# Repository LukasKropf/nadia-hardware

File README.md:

# NADIA - Hardware

- 3 galvanisch getrennte RS-232 Schnittstellen, [MAX33250EELC+](https://media.digikey.com/pdf/Data%20Sheets/Maxim%20PDFs/MAX33250E_51E_Rev1_Nov2018.pdf)
- 5 digitale Eingänge
- 5 analoge Eingänge
- 3 galvanisch getrennte Ausgänge (Solid State Relais, [G3VM-61GR2](https://omronfs.omron.com/en_US/ecb/products/pdf/en-g3vm_41gr8_61gr.pdf))
- Galvanisch getrennte PoE Speisung

## Übersicht

``` mermaid
flowchart LR
    A[M12 Ethernet mit PoE] --- B[NADIA]
    B --- C[5 Digitale Eingänge]
    B --- D[5 Analoge Eingänge]
    B --- E[3 RS-232 Schnittstellen]
    B --- F[3 Digitale Ausgänge]    
    G[Optionale Speisung] -.- B
    H[micro-USB] -.- B
    I[micro-SD Karte] --- B
    
```
|NADIA im Gehäuse | NADIA PCB |
|-|-|
|  ||

## Rechnerplatine

| Wert                                      | Wert       | Einheit |
|:------------------------------------------|------------|---------|
| Rechnerplatine  [Pocketbeagle](https://beagleboard.org/pocket)                          |  |   -    |
| RAM                                       |  512       | MB,  DDR3 RAM|
| CPU  [Octavo Systems OSD3358-SM](http://octavosystems.com/octavo_products/osd335x-sm/)          |  1         | GHz           |
| Speicher                                  |  -         | microSD       |

## Elektrische Charakteristik

| Wert                                      | Min  | Typisch  | Max       | Einheit |
|:------------------------------------------|------|:--------:|-----------|---------|
| Speisung Spannung                         | 36   | 48       | 56        | VDC       |
| Speisung Strom                            |      | 50       | 100       | mA      |
| Galvanische Trennung Speisung             |      |          | 1.5       | kV      |
| **Digitaler Eingang**                     |
| Schmitt-Trigger [74HC7014D](https://www.mouser.ch/datasheet/2/916/74HC7014-1598223.pdf)    |
| Digitaler Eingang Pegel High              |      | 4        |           | VDC       |
| Digitaler Eingang Pegel Low               |      | 3.8      |           | VDC       |
| Digitaler Eingang maximale Spannung       | -100 |          | 100       | VDC       |
| Digitaler Eingang Eingangswiderstand      | 560  |          | 660       | kΩ      |
| **Analoger Eingang**                      |
| Spannungsteiler mit Widerständen|
| Analoger Eingang maximale Spannung        | -100 |          | 100       | VDC       |
| Analoger Eingang Messbereich / V          | 0    |          | 50        | VDC       |
| Analoger Eingang Eingangswiderstand       | 560  |          | 850       | kΩ      |
| Analoger Eingang Bandbreite -3dB          |      | 300      |           | Hz      |
| **Digitaler Ausgang**                     |
| Solid State Relais [G3VM-61GR2](https://omronfs.omron.com/en_US/ecb/products/pdf/en-g3vm_41gr8_61gr.pdf) |
| Digitaler Ausgang Spannung                |      |          | 60        | Vpeak AC/DC   |
| Digitaler Ausgang Strom                   |      |          | 1.7       | A       |
| Digitaler Ausgang Schaltfrequent          |      |          | 10        | Hz      |
| Digitaler Ausgang Isolationsspannung      |      |          | 1.5       | kV_rms  |
| **RS-232 Schnittstelle**                  |
| Treiber  [MAX33250EELC+](https://media.digikey.com/pdf/Data%20Sheets/Maxim%20PDFs/MAX33250E_51E_Rev1_Nov2018.pdf)| ||||
| RS-232 Schnittstelle Galvanische Trennung |      | 200      | 600 @ 60s | Vrms    |
| RS-232 ESD Schutz                         |      |          | ±15       | kV      |
| RS-232 Eingangswiderstand                  | 3    | 5        | 7         | kΩ      |
| RS-232 Eingangsspannung                    |      |          | ±25       | V       |
| RS-232 Ausgangsspannung                   |      | ±5 @ 3kΩ | ±13.2     | V       |
| RS-232 Ausgangskurzschlussstrom          |      |          | ±70       | mA      |

## Konnektivität

### Ethernet

Die Ethernetverbindung wird NADIA intern über einen USB-Ethernet Wandler sichergestellt, dem [LAN9500A von Microchip](https://www.microchip.com/en-us/product/LAN9500A).

Über Ethernet kann auf alle Dienste von NADIA zugegriffen werden.

### Micro USB

Auf NADA kann über die Micro USB Schnittstelle zugegriffen werden. NADIA erstellt über USB eine virtuelle Ethernet-Verbindung her.
Mehr Details siehe die Dokumentation von Beagleboard Pocketbeagle:

- [Getting Started - Enable a network connection](https://beagleboard.org/getting-started#step2)
- [Pocketbeagle System Reference Manual](https://github.com/beagleboard/pocketbeagle/wiki/System-Reference-Manual#533-usb-20-connector)

Über USB kann auf alle Dienste von NADIA zugegriffen werden.

### Wireless

NADIA verfügt über keine Wireless Kommunikationsmöglichkeiten.

### CAN

NADIA verfügt in dieser Version über **kein** CAN.
Allerdings verfügt das Pocketbeagle über die Möglichkeit zwei CAN Schnittstellen anzubinden. Dies würde ein neues PCB-Layout voraussetzen.

### Serial RS232

Die drei seriellen Schnittstellen sind jeweils galvanisch getrennt von der Speisung. Aus Sicherheitsgründen müssen die Schnittstellen über einen GPIO Pin freigeschaltet werden, bevor sie benutzt werden können.

## Software

Als Basisimage dient das Image von Pocketbeagle:
[AM3358 Debian 10.3 2020-04-06 4GB SD IoT](https://beagleboard.org/latest-images)
Um einen zuverlässigen Betrieb sicherzustellen, ist die Erstellung von verschiedenen Partitionen nötig. Die Systempartition in ReadOnly.

[Node-RED](https://nodered.org/) wird für das eigentliche Programmieren verwendet.
Mit Node-RED können auch sehr einfach ansprechende GUIs erstellt werden.

Auf NADIA, respektive dem PocketBeagle, ist auch jede andere ARMHF Linux Software lauffähig.

Beispiele: (jedoch noch keine Erfahrung)

- [OpenPLC](https://www.openplcproject.com/)
- [4DIAC](https://www.eclipse.org/4diac/)

# Licence

Copyright Lukas Kropf 2022.

This source describes Open Hardware and is licensed under the CERN-OHL-W v2  or later.

You may redistribute and modify this documentation and make products
using it under the terms of the CERN-OHL-W v2 (https:/cern.ch/cern-ohl).

This documentation is distributed WITHOUT ANY EXPRESS OR IMPLIED
WARRANTY, INCLUDING OF MERCHANTABILITY, SATISFACTORY QUALITY
AND FITNESS FOR A PARTICULAR PURPOSE. 
Please see the CERN-OHL-W v2 for applicable conditions.

Source location: https://github.com/LukasKropf/nadia-hardware

As per CERN-OHL-W v2 section 4.1, should You produce hardware based on
these sources, You must maintain the Source Location visible on the
external case of NADIA-Hardware or other product you make using
this documentation.

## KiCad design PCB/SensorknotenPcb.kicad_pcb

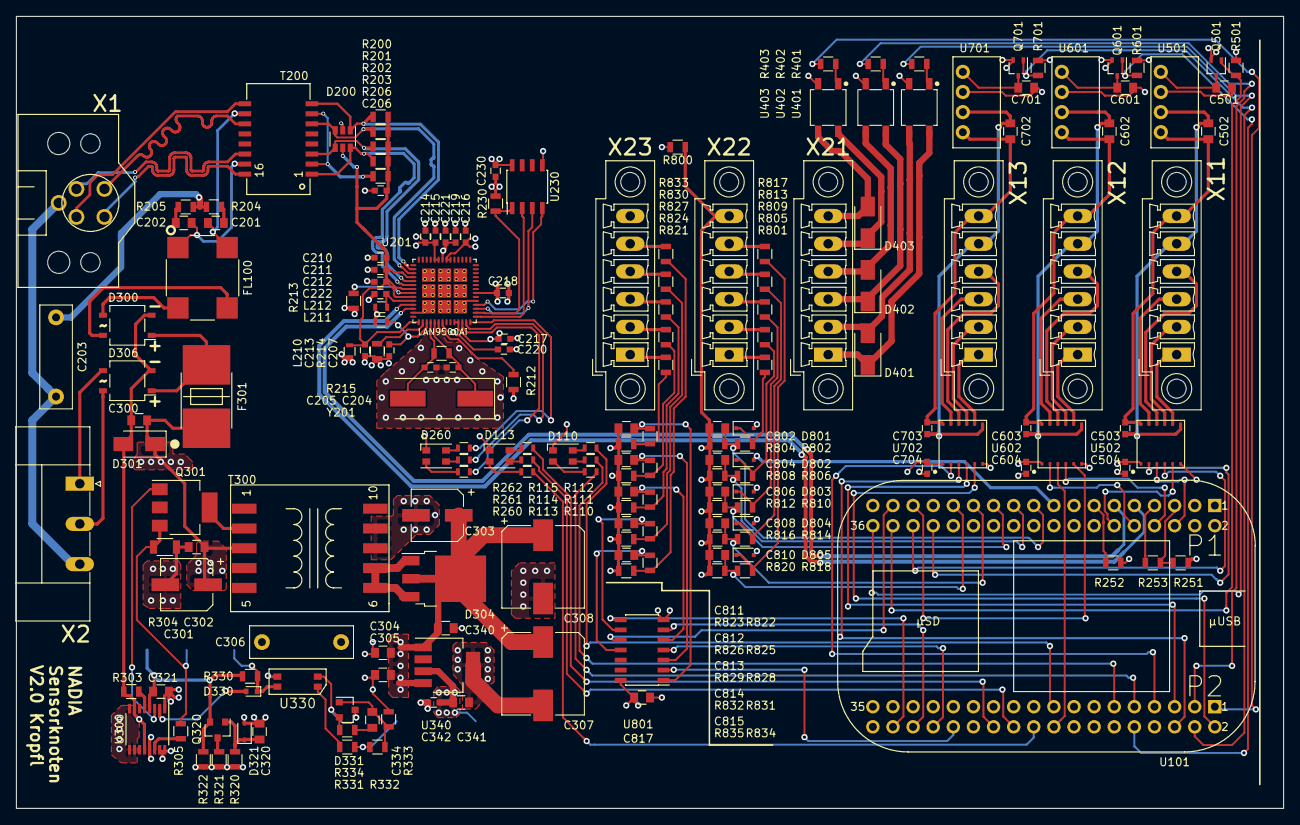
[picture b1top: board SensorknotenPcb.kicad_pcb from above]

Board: 4 copper layers, 160.0 x 100.0 mm, 193 parts (0 on the bottom side), 161 nets.

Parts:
C201, C202: 22n/200V; C_0805
C203, C306: 1n/2kV; C_Rect_L13.0mm_W4.0mm_P10.00mm_FKS3_FKP3_MKS4
C204, C205: 33pF 50V; C_0603
C206, C207, C210, C211, C212, C213, C214, C215, C216, C217, C218, C219, C220, C221, C222, C230, C342, C503, C504, C603, C604, C703, C704: 0.1µF; C_0603
C300: 0.1µF 100V; C_0805
C301: 10µF 63V; CP_Elec_6.3x5.8
C302: 1µF; C_0805
C303: 330µF; CP_Elec_6.3x5.8
C304, C305, C321, C340, C341, C501, C502, C601, C602, C701, C702, C817: 10µF; C_0805
C307, C308: 1500µF; CP_Elec_10x10
C320, C802, C804, C806, C808, C810, C811, C812, C813, C814, C815: 47nF; C_0805
C334: 6.8nF; C_0805
D110, D113, D260: LED_ARGB; LED_Cree-PLCC4_3.2x2.8mm_CCW
D200: WE-TVS_5V; SOT-23-6
D300, D306: D_Bridge_+-AA; Diode_Bridge_TO-269AA
D301: TVS 58V; D_SMA
D304: D_Schottky; TO-252-3_TabPin2
D321: 9.1V; D_SOD-323
D330: Fast Recovery; D_SOD-523
D331: TLV431BCDBZR; SOT-23
D401, D402, D403: TVS_45V; D_SMA
D801, D802, D803, D804, D805: 24V; D_SOD-323F
F301: 0.35A; FuseHolder_Schurter_0031.7701.11
FL100: EMI_Filter_Common_WE; CommonModeChoke_WuerthType-WE-SL5
L210, L211, L212: Ferrite_Bead; L_0603
Q301: Q_NMOS_GDSD; SOT-223
Q320: Q_NPN_BEC; SOT-23
Q501, Q601, Q701: DMG1012UW-7; SOT-323_SC-70
R110, R113, R260: 240; R_0603
R111, R112, R114, R115, R261, R262: 62; R_0603
R200, R201, R202, R203: 49.9 1%; R_0805
R204, R205: 75; R_0805
R206, R212, R251, R252, R253, R800: 0R; R_0805
R213, R214: 12k 1%; R_0805
R215, R303: open; R_0805
R230, R305, R334: 10k; R_0805
R304: 0.05 1%; R_1206
R320, R322: 220k; R_0805
R321: 100; R_0805
R330: 6k8; R_0805
R331, R822, R825, R828, R831, R834: 1k; R_0805
R332, R501, R601, R701: 100k; R_0805
R333: 33k; R_0805
R401, R402, R403: 200; R_0805
R801, R802, R805, R806, R809, R810, R813, R814, R817, R818, R821, R823, R824, R826, R827, R829, R830, R832, R833, R835: 560k; R_0805
R804, R808, R812, R816, R820: 43k; R_0805
T200: 749013011A; WE-LAN_PoE_749013011A
T300: WE_750310013; WE_EP13
TP301: R304_Shunt; Measurement_Point_Round-SMD-Pad_Small
TP320: TP_Pvcc; Measurement_Point_Round-SMD-Pad_Small
TP330: TP_U300_run; Measurement_Point_Round-SMD-Pad_Small
TP331: TP_Opto5V; Measurement_Point_Round-SMD-Pad_Small
TP340: TP_3.3V; Measurement_Point_Round-SMD-Pad_Small
TP341: TP_5V; Measurement_Point_Round-SMD-Pad_Small
U101: PocketBeagle
U201: LAN9500Ai; QFN50P800X800X120-56N
U230: 93AA56A; SOIC-8_3.9x4.9mm_Pitch1.27mm
U300: LTC4267; SSOP-16_3.9x4.9mm_Pitch0.635mm
U330: PS2911; DIP-4_SMD_Opto
U340: LP38693MP-3.3; SOT-223-5
U401, U402, U403: G3VM-61VR(TR05); SOP-4_3.9x4.4mm_Pitch2.54mm
U501, U601, U701: RFM-0505S; RFM-xxxxS
U502, U602, U702: MAX33250E_51E; LGA-12
U801: 74HC7014D-118; SOIC-14_3.9x8.7mm_Pitch1.27mm
X1: Phoenix_1436550; Phoenix_SACC-DSIV-M12FSD-4CON-L90
X2: Phoenix_1847479; PhoenixContact_MC-GF_03x5.08mm_Angled_ThreadedFlange
X11, X12, X13, X21, X22, X23: Phoenix_1843266; PhoenixContact_MCV-GF_06x3.50mm_Vertical_ThreadedFlange_Mou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
Y201: 25.000MHz 18pF; Crystal_SMD_HC49-SD

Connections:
+3V3: C214.1, C215.1, C216.1, C217.1, C218.1, C230.1, C341.1, C342.1, C504.1, C604.1, C704.1, C817.1, D110.1, D113.1, D260.1, L210.2, R212.1, TP340.1, U201.24, U201.25, U201.35, U201.48, U201.49, U201.51, U201.52, U230.8, U340.3, U502.1, U602.1, U702.1, U801.14
+5V: C303.1, C304.1, C305.1, C307.1, C308.1, C340.1, C501.1, C601.1, C701.1, D304.2, R251.1, R331.1, R332.1, TP341.1, U101.101, U340.1, U340.4, U501.2, U601.2, U701.2
/106_SPI0.CS: U101.106, U502.3
/108_SPI0.CLK: U101.108, U602.4
/110_SPI0.MISO: U101.110, U602.2
/112_SPI0.MOSI: U101.112, U502.5
/119_AIN0_1.8V: C802.1, R802.1, R804.2, U101.119
/121_AIN1_1.8V: C804.1, R806.1, R808.2, U101.121
/123_AIN2_1.8V: C806.1, R810.1, R812.2, U101.123
/125_AIN3_1.8V: C808.1, R814.1, R816.2, U101.125
/127_AIN4_1.8V: C810.1, R818.1, R820.2, U101.127
/130_UART0.TX: U101.130, U502.2
/131_PRU-0.4: U101.131, U602.5
/132_UART0.RX: U101.132, U502.4
/133_PRU-0.1: U101.133, U801.10
/134_GPIO-0.26: Q501.1, R501.1, U101.134
/136_PWM0A: R401.2, U101.136
/201_PWM1A: R403.2, U101.201
/202_GPIO-1.27: U101.202, U702.5
/203_GPIO-0.23: R402.2, U101.203
/204_GPIO-1.26: Q701.1, R701.1, U101.204
/205_UART4.RX: U101.205, U702.4
/206_GPIO-1.25: U101.206, U702.3
/207_UART4.TX: U101.207, U702.2
/209_I2C1.SCL: R110.2, U101.209
/210_GPIO-1.20: Q601.1, R601.1, U101.210
/211_I2C1.SDA: R111.2, U101.211
/217_GPIO-2.1: R112.2, U101.217
/218_PRU-0.15: U101.218, U602.3
/220_GPIO-2.0: R113.2, U101.220
/222_GPIO-1.14: R114.2, U101.222
/224_GPIO-1.12: R115.2, U101.224
/228_PRU-0.6: U101.228, U801.2
/230_PRU-0.3: U101.230, U801.4
/232_PRU-0.2: U101.232, U801.6
/234_PRU-0.5: U101.234, U801.8
/Analoge und Digitale Eingänge/Ain0: R801.1, X22.1
/Analoge und Digitale Eingänge/Ain1: R805.1, X22.2
/Analoge und Digitale Eingänge/Ain2: R809.1, X22.3
/Analoge und Digitale Eingänge/Ain3: R813.1, X22.4
/Analoge und Digitale Eingänge/Ain4: R817.1, X22.5
/Analoge und Digitale Eingänge/Din0: R821.2, X23.1
/Analoge und Digitale Eingänge/Din1: R824.2, X23.2
/Analoge und Digitale Eingänge/Din2: R827.2, X23.3
/Analoge und Digitale Eingänge/Din3: R830.2, X23.4
/Analoge und Digitale Eingänge/Din4: R833.2, X23.5
/Digitale Ausgänge/In0: D401.1, U401.4, X21.1
/Digitale Ausgänge/In1: D402.1, U402.4, X21.3
/Digitale Ausgänge/In2: D403.1, U403.4, X21.5
/Digitale Ausgänge/Out0: D401.2, U401.3, X21.2
/Digitale Ausgänge/Out1: D402.2, U402.3, X21.4
/Digitale Ausgänge/Out2: D403.2, U403.3, X21.6
/PoE und Speisung/DataPairR: C202.1, FL100.1, T200.15
/PoE und Speisung/DataPairT: C201.1, FL100.4, T200.10
/PoE und Speisung/Pvcc: C321.1, Q320.2, R322.2, R330.1, TP320.1, U300.4
/PoE und Speisung/VportN: C300.2, D300.2, D301.2, D306.2, R303.2, U300.7, U300.12
/PoE und Speisung/VportP: C300.1, C301.1, C302.1, D301.1, F301.1, R320.1, R321.1, R322.1, T300.3, U300.13
/PoE und Speisung/run: D330.2, U300.2
/RS232GalvIsol_0/5V_isol: C502.1, C503.1, U501.4, U502.12, X11.6
/RS232GalvIsol_0/CtsIsol: U502.8, X11.1
/RS232GalvIsol_0/DtrIsol: U502.10, X11.4
/RS232GalvIsol_0/GND_isol: C502.2, C503.2, U501.3, U502.7, X11.5
/RS232GalvIsol_0/RxIsol: U502.9, X11.2
/RS232GalvIsol_0/TxIsol: U502.11, X11.3
/RS232GalvIsol_2/5V_isol: C602.1, C603.1, U601.4, U602.12, X12.6
/RS232GalvIsol_2/CtsIsol: U602.8, X12.1
/RS232GalvIsol_2/DtrIsol: U602.10, X12.4
/RS232GalvIsol_2/GND_isol: C602.2, C603.2, U601.3, U602.7, X12.5
/RS232GalvIsol_2/RxIsol: U602.9, X12.2
/RS232GalvIsol_2/TxIsol: U602.11, X12.3
/USB1.D+: U101.111, U201.12
/USB1.D-: U101.109, U201.11
/USB1.ID: R252.1, U101.113
/USB1.VBUS: R251.2, R253.1, U101.105
/USB1.VIN: R253.2, U101.107
/UsbAndEthernet/EECLK: U201.29, U230.2
/UsbAndEthernet/EECS: R230.1, U201.30, U230.1
/UsbAndEthernet/EEDI: U201.32, U230.4
/UsbAndEthernet/EEDO: U201.31, U230.3
/UsbAndEthernet/Rd+: D200.6, R203.2, T200.1, U201.6
/UsbAndEthernet/Rd-: D200.4, R202.2, T200.3, U201.5
/UsbAndEthernet/Rx+: T200.16, X1.2
/UsbAndEthernet/Rx-: T200.14, X1.4
/UsbAndEthernet/Td+: D200.3, R201.2, T200.6, U201.3
/UsbAndEthernet/Td-: D200.1, R200.2, T200.8, U201.2
/UsbAndEthernet/Tx+: T200.11, X1.1
/UsbAndEthernet/Tx-: T200.9, X1.3
/UsbAndEthernet/VDD33A: C206.1, C210.1, C211.1, C212.1, C213.1, D200.5, L210.1, R200.1, R201.1, R202.1, R203.1, R206.1, U201.4, U201.7, U201.9, U201.15
/UsbAndEthernet/VDDCORE: C219.1, C220.1, C221.1, L211.2, L212.2, U201.21, U201.50
/UsbAndEthernet/VDDPLL: C222.1, L212.1, U201.10
/UsbAndEthernet/VDDUSBPLL: C207.1, L211.1, U201.17
/UsbAndEthernet/nFDX_LED: R260.2, U201.26
/UsbAndEthernet/nLNKA_LED: R261.2, U201.27
/UsbAndEthernet/nSPD_LED: R262.2, U201.28
/sheet5CAA8AE_4/5V_isol: C702.1, C703.1, U701.4, U702.12, X13.6
/sheet5CAA8AE_4/CtsIsol: U702.8, X13.1
/sheet5CAA8AE_4/DtrIsol: U702.10, X13.4
/sheet5CAA8AE_4/GND_isol: C702.2, C703.2, U701.3, U702.7, X13.5
/sheet5CAA8AE_4/RxIsol: U702.9, X13.2
/sheet5CAA8AE_4/TxIsol: U702.11, X13.3
Earth_Protective: C203.2, X1.5, X2.3
GND: C204.2, C205.2, C206.2, C207.2, C210.2, C211.2, C212.2, C213.2, C214.2, C215.2, C216.2, C217.2, C218.2, C219.2, C220.2, C221.2, C222.2, C230.2, C303.2, C304.2, C305.2, C306.2, C307.2, C308.2, C340.2, C341.2, C342.2, C504.2, C604.2, C704.2, C811.2, C812.2, C813.2, C814.2, C815.2, C817.2, D200.2, D331.3, Q501.2, Q601.2, Q701.2, R213.1, R214.1, R230.2, R252.2, R333.2, R501.2, R601.2, R701.2, R800.2, R823.2, R826.2, R829.2, R832.2, R835.2, T300.7, T300.8, U101.115, U101.116, U101.122, U101.215, U101.221, U201.13, U201.33, U201.57, U230.5, U340.5, U401.2, U402.2, U403.2, U502.6, U602.6, U702.6, U801.7, X23.6
GNDA: C802.2, C804.2, C806.2, C808.2, C810.2, D801.2, D802.2, D803.2, D804.2, D805.2, R800.1, R804.1, R808.1, R812.1, R816.1, R820.1, U101.117, X22.6
GNDPWR: C301.2, C302.2, C306.1, C320.2, C321.2, D321.2, R304.2, U300.1, U300.8, U300.9, U300.10, U300.15, U300.16, U330.3
unnamed: C201.2, R204.1
unnamed: C202.2, R205.1
unnamed: C203.1, R204.2, R205.2
unnamed: C204.1, R215.2, U201.19, Y201.1
unnamed: C205.1, R215.1, U201.18, Y201.2
unnamed: C320.1, D321.1, Q320.1, R320.2
unnamed: C334.1, D331.1, R332.2, R333.1
unnamed: C334.2, R334.1
unnamed: C501.2, Q501.3, U501.1
unnamed: C601.2, Q601.3, U601.1
unnamed: C701.2, Q701.3, U701.1
unnamed: C811.1, R822.1, U801.1
unnamed: C812.1, R825.1, U801.3
unnamed: C813.1, R828.1, U801.5
unnamed: C814.1, R831.1, U801.9
unnamed: C815.1, R834.1, U801.11
unnamed: D110.2, R110.1
unnamed: D110.3, R111.1
unnamed: D110.4, R112.1
unnamed: D113.2, R113.1
unnamed: D113.3, R114.1
unnamed: D113.4, R115.1
unnamed: D260.2, R260.1
unnamed: D260.3, R261.1
unnamed: D260.4, R262.1
unnamed: D300.1, D306.1, F301.2
unnamed: D300.3, FL100.2
unnamed: D300.4, FL100.3
unnamed: D304.1, D304.3, T300.9, T300.10
unnamed: D306.3, X2.1
unnamed: D306.4, X2.2
unnamed: D330.1, R330.2, TP330.1, U330.4
unnamed: D331.2, R334.2, TP331.1, U330.2
unnamed: D801.1, R801.2, R802.2
unnamed: D802.1, R805.2, R806.2
unnamed: D803.1, R809.2, R810.2
unnamed: D804.1, R813.2, R814.2
unnamed: D805.1, R817.2, R818.2
unnamed: Q301.1, U300.3
unnamed: Q301.3, R304.1, R305.1, TP301.1
unnamed: Q301.4, T300.4
unnamed: Q320.3, R321.2
unnamed: R206.2, T200.2, T200.7
unnamed: R212.2, U201.20
unnamed: R213.2, U201.8
unnamed: R214.2, U201.16
unnamed: R303.1, U300.5
unnamed: R305.2, U300.14
unnamed: R331.2, U330.1
unnamed: R401.1, U401.1
unnamed: R402.1, U402.1
unnamed: R403.1, U403.1
unnamed: R821.1, R822.2, R823.1
unnamed: R824.1, R825.2, R826.1
unnamed: R827.1, R828.2, R829.1
unnamed: R830.1, R831.2, R832.1
unnamed: R833.1, R834.2, R835.1

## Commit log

2022-10-30 Initialer Upload
2024-04-24 Update README.md
    Hardware Beschreibung hinzugefügt
2024-04-24 Neue Bilder hochgeladen
2024-04-24 Update README.md
    Bilder vom PCB und Gehäuse in eine Tabelle verschoben
